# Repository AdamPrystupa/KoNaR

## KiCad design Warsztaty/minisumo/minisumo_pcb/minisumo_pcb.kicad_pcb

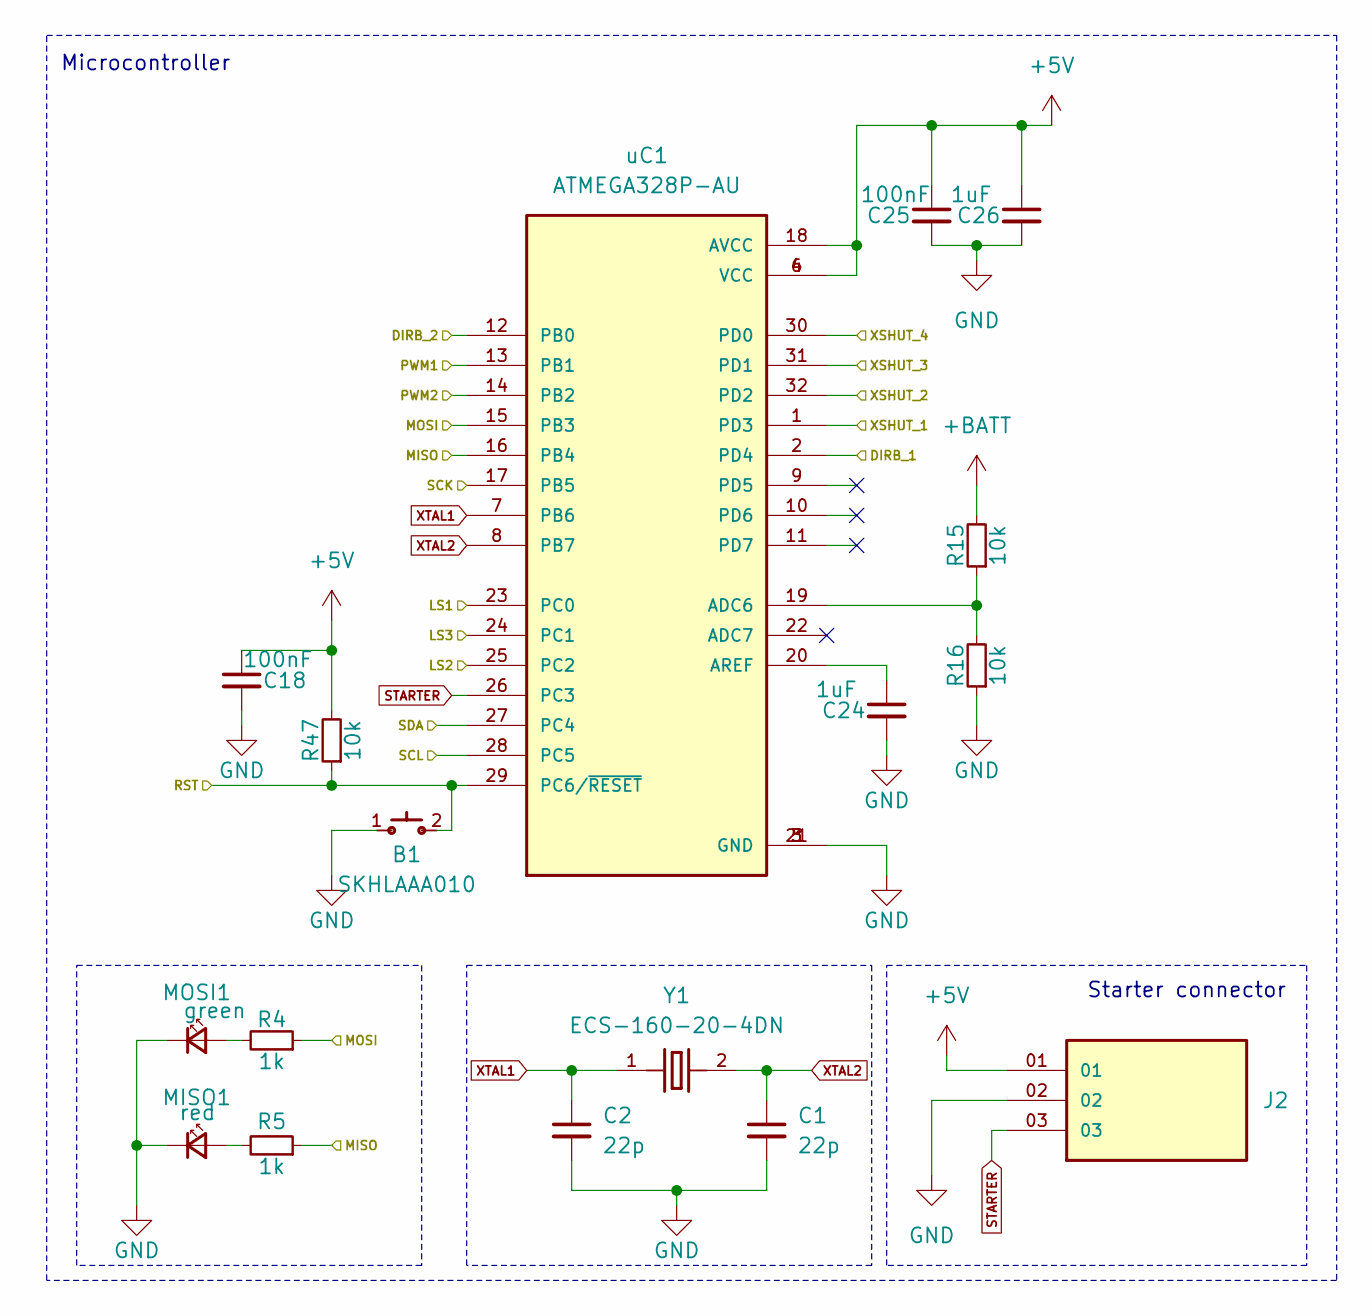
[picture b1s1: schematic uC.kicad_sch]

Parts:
B1: SKHLAAA010
C1, C2: 22p; C_0805_2012Metric
C18, C25: 100nF; C_0805_2012Metric
C24, C26: 1uF; C_0805_2012Metric
J2: MTSW-103-23-F-S-235; SAMTEC_MTSW-103-23-F-S-235; PARTREV R
MISO1: red; LED_0805_2012Metric
MOSI1: green; LED_0805_2012Metric
R4, R5: 1k; R_0805_2012Metric
R15, R16: 10k; R_0805_2012Metric
R47: 10k; R_0805_2012Metric_Pad1.20x1.40mm_HandSolder
Y1: ECS-160-20-4DN; XTAL_ECS-160-20-4DN
uC1: ATMEGA328P-AU; QFP80P900X900X120-32N; PARTREV 8271A

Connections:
+5V: C18.1, C25.1, C26.1, J2.01, R47.2, uC1.4 (VCC), uC1.6 (VCC), uC1.18 (AVCC); also elsewhere on the board
+BATT: R15.2; also elsewhere on the board
/inverter/DIRB_1: uC1.2 (PD4); also elsewhere on the board
/inverter/DIRB_2: uC1.12 (PB0); also elsewhere on the board
/line_sensors/LS1: uC1.23 (PC0); also elsewhere on the board
/line_sensors/LS2: uC1.25 (PC2); also elsewhere on the board
/line_sensors/LS3: uC1.24 (PC1); also elsewhere on the board
/motor_driver1/PWM1: uC1.13 (PB1); also elsewhere on the board
/motor_driver2/PWM2: uC1.14 (PB2); also elsewhere on the board
/programming_connector/MISO: R5.1, uC1.16 (PB4); also elsewhere on the board
/programming_connector/MOSI: R4.1, uC1.15 (PB3); also elsewhere on the board
/programming_connector/RST: B1.2, R47.1, uC1.29 (PC6/~RESET); also elsewhere on the board
/programming_connector/SCK: uC1.17 (PB5); also elsewhere on the board
/sensor1/SCL: uC1.28 (PC5); also elsewhere on the board
/sensor1/SDA: uC1.27 (PC4); also elsewhere on the board
/sensor1/XSHUT_1: uC1.1 (PD3); also elsewhere on the board
/sensor2/XSHUT_2: uC1.32 (PD2); also elsewhere on the board
/sensor3/XSHUT_3: uC1.31 (PD1); also elsewhere on the board
/sensor4/XSHUT_4: uC1.30 (PD0); also elsewhere on the board
GND: B1.1, C1.2, C2.2, C18.2, C24.2, C25.2, C26.2, J2.02, MISO1.1 (K), MOSI1.1 (K), R16.1, uC1.3 (GND), uC1.5 (GND), uC1.21 (GND); also elsewhere on the board
unnamed: MISO1.2 (A), R5.2
unnamed: MOSI1.2 (A), R4.2
unnamed: R15.1, R16.2, uC1.19 (ADC6)
unnamed: C24.1, uC1.20 (AREF)
STARTER: J2.03, uC1.26 (PC3)
XTAL1: C2.1, Y1.1, uC1.7 (PB6)
XTAL2: C1.1, Y1.2, uC1.8 (PB7)

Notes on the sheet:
Starter connector
Microcontroller

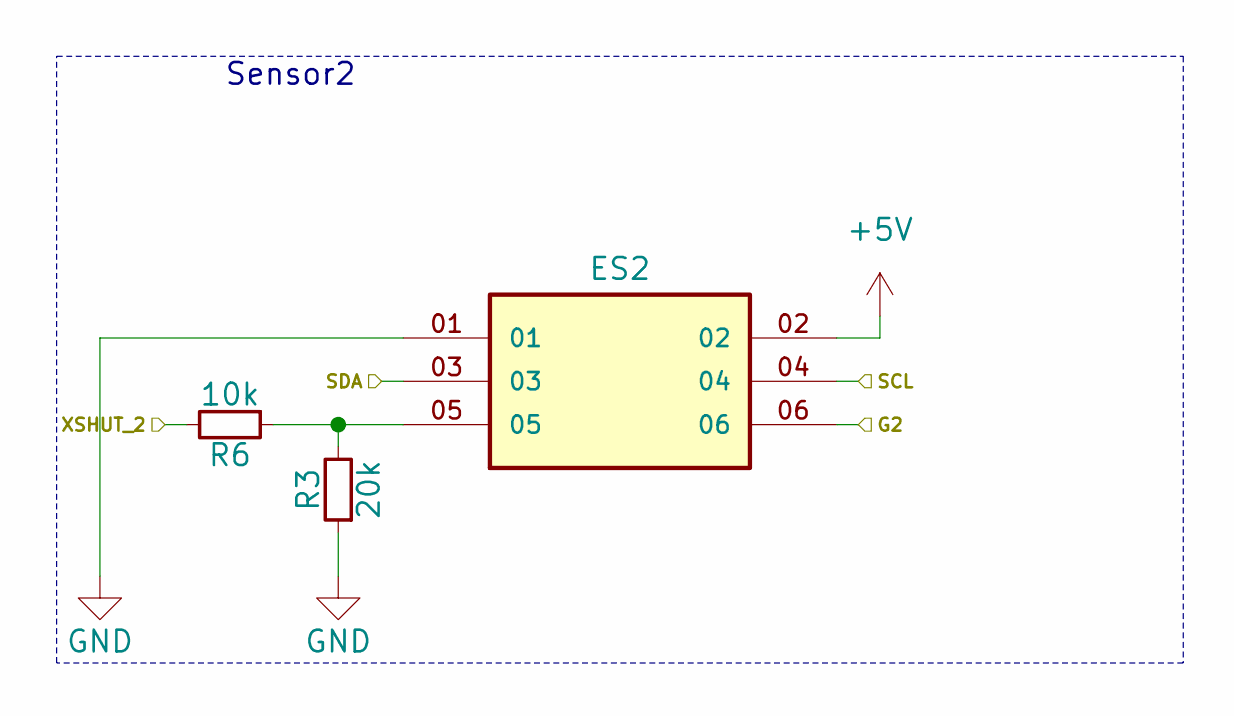
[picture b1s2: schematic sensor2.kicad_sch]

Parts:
ES2: MTSW-103-23-F-D-230; SAMTEC_MTSW-103-23-F-D-230; PARTREV R
R3: 20k; R_0805_2012Metric
R6: 10k; R_0805_2012Metric

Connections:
+5V: ES2.02; also elsewhere on the board
/sensor1/SCL: ES2.04; also elsewhere on the board
/sensor1/SDA: ES2.03; also elsewhere on the board
/sensor2/G2: ES2.06
/sensor2/XSHUT_2: R6.2; also elsewhere on the board
GND: ES2.01, R3.1; also elsewhere on the board
unnamed: ES2.05, R3.2, R6.1

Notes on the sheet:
Sensor2

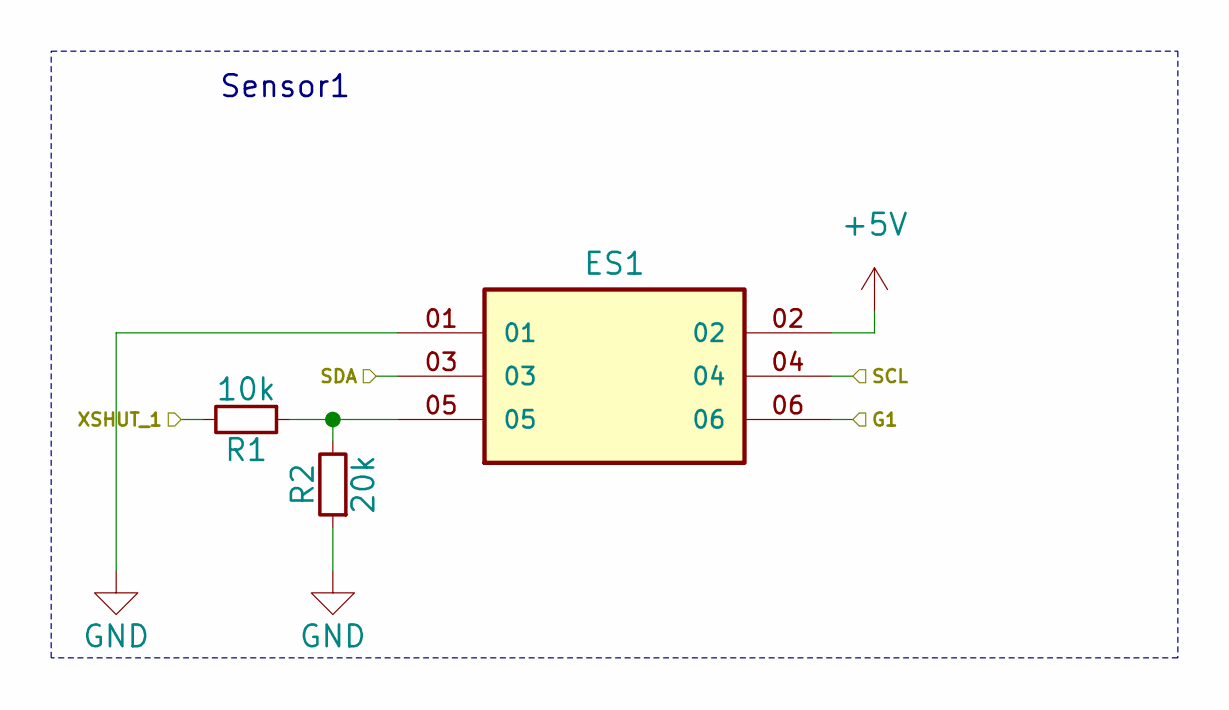
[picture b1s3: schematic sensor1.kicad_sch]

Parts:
ES1: MTSW-103-23-F-D-230; SAMTEC_MTSW-103-23-F-D-230; PARTREV R
R1: 10k; R_0805_2012Metric
R2: 20k; R_0805_2012Metric

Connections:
+5V: ES1.02; also elsewhere on the board
/sensor1/G1: ES1.06
/sensor1/SCL: ES1.04; also elsewhere on the board
/sensor1/SDA: ES1.03; also elsewhere on the board
/sensor1/XSHUT_1: R1.2; also elsewhere on the board
GND: ES1.01, R2.1; also elsewhere on the board
unnamed: ES1.05, R1.1, R2.2

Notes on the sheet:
Sensor1

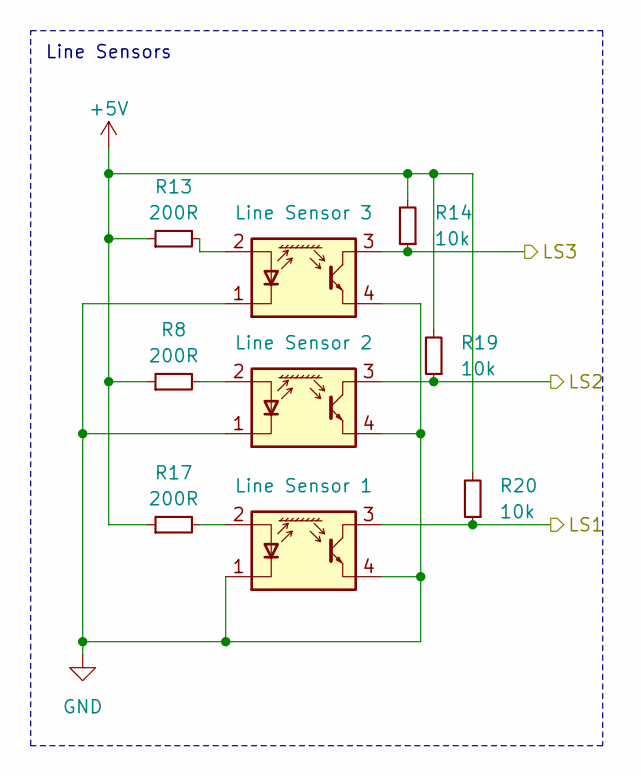
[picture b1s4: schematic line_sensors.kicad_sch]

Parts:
LS1, LS2, LS3: ITR8307-S17-TR8; Everlight_ITR1201SR10AR
R8, R13, R17: 200R; R_0805_2012Metric
R14, R19, R20: 10k; R_0805_2012Metric

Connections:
+5V: R8.1, R13.1, R14.2, R17.1, R19.2, R20.2; also elsewhere on the board
/line_sensors/LS1: LS1.3, R20.1; also elsewhere on the board
/line_sensors/LS2: LS2.3, R19.1; also elsewhere on the board
/line_sensors/LS3: LS3.3, R14.1; also elsewhere on the board
GND: LS1.1 (K), LS1.4, LS2.1 (K), LS2.4, LS3.1 (K), LS3.4; also elsewhere on the board
unnamed: LS1.2 (A), R17.2
unnamed: LS2.2 (A), R8.2
unnamed: LS3.2 (A), R13.2

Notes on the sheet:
Line Sensors

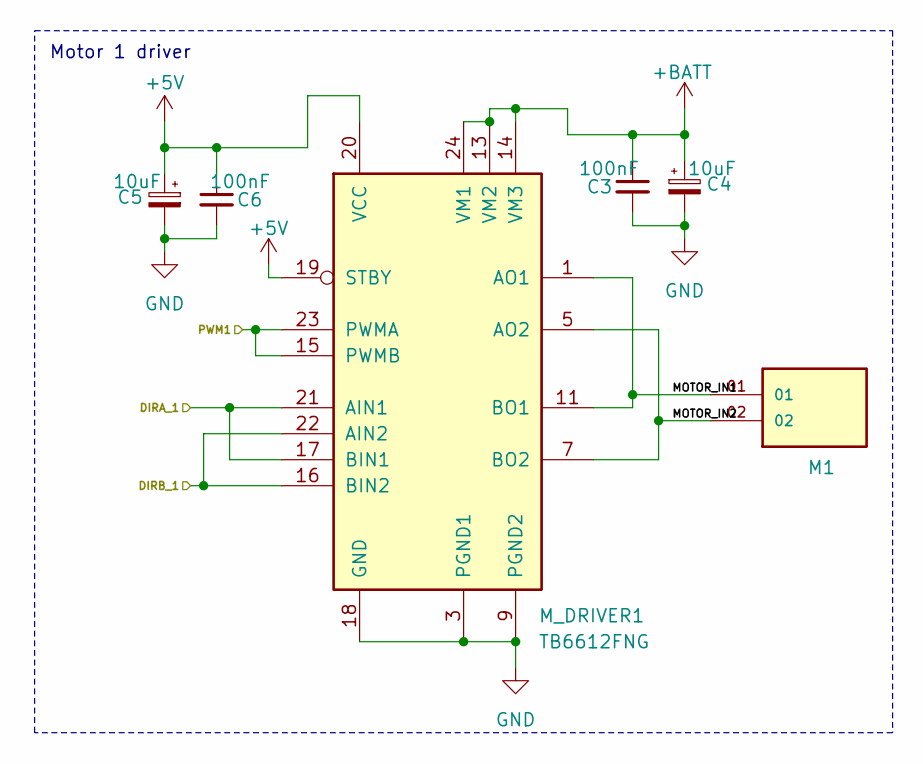
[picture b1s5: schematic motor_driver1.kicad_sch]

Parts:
C3, C6: 100nF; C_0805_2012Metric
C4, C5: 10uF; CP_EIA-3528-12_Kemet-T
M1: HTSW-102-08-L-S; SAMTEC_HTSW-102-08-L-S
M_DRIVER1: TB6612FNG; SSOP-24_5.3x8.2mm_P0.65mm

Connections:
+5V: C5.1, C6.1, M_DRIVER1.19 (STBY), M_DRIVER1.20 (VCC); also elsewhere on the board
+BATT: C3.1, C4.1, M_DRIVER1.13 (VM2), M_DRIVER1.14 (VM3), M_DRIVER1.24 (VM1); also elsewhere on the board
/inverter/DIRA_1: M_DRIVER1.17 (BIN1), M_DRIVER1.21 (AIN1); also elsewhere on the board
/inverter/DIRB_1: M_DRIVER1.16 (BIN2), M_DRIVER1.22 (AIN2); also elsewhere on the board
/motor_driver1/MOTOR_IN1: M1.01, M_DRIVER1.1 (AO1), M_DRIVER1.2 (AO1), M_DRIVER1.11 (BO1), M_DRIVER1.12 (BO1)
/motor_driver1/MOTOR_IN2: M1.02, M_DRIVER1.5 (AO2), M_DRIVER1.6 (AO2), M_DRIVER1.7 (BO2), M_DRIVER1.8 (BO2)
/motor_driver1/PWM1: M_DRIVER1.15 (PWMB), M_DRIVER1.23 (PWMA); also elsewhere on the board
GND: C3.2, C4.2, C5.2, C6.2, M_DRIVER1.3 (PGND1), M_DRIVER1.4 (PGND1), M_DRIVER1.9 (PGND2), M_DRIVER1.10 (PGND2), M_DRIVER1.18 (GND); also elsewhere on the board

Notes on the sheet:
Motor 1 driver

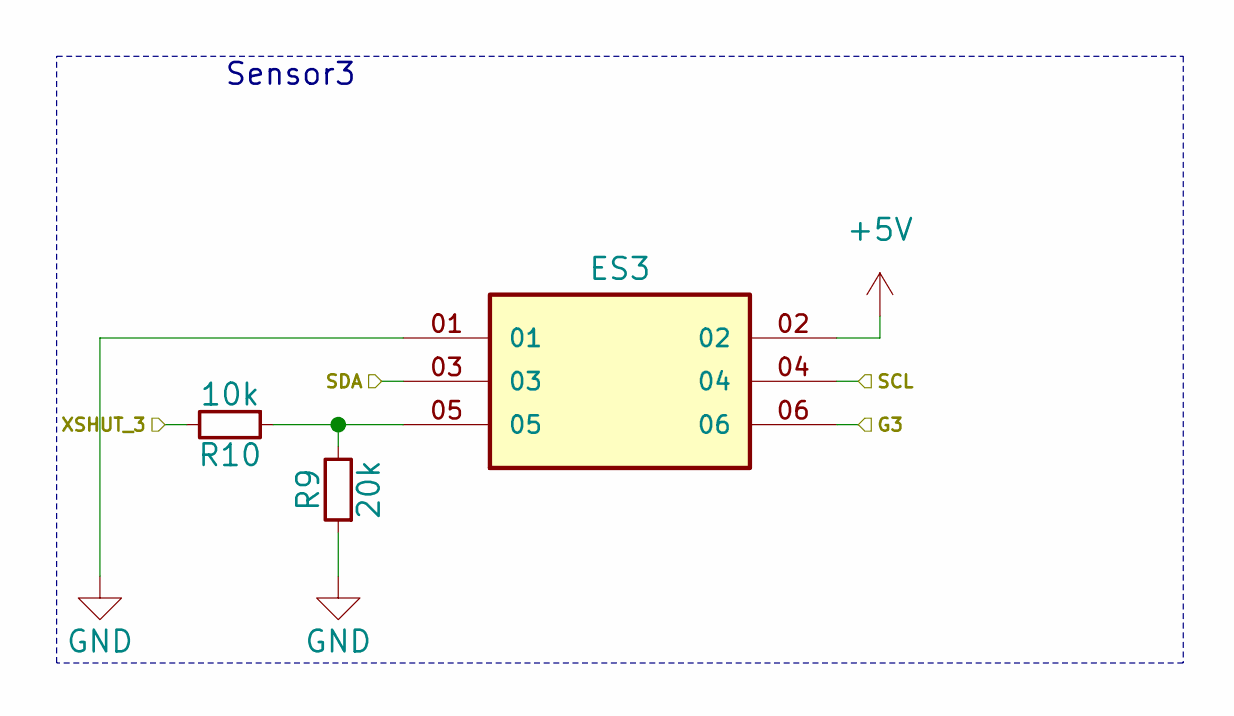
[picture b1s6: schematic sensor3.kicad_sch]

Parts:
ES3: MTSW-103-23-F-D-230; SAMTEC_MTSW-103-23-F-D-230; PARTREV R
R9: 20k; R_0805_2012Metric
R10: 10k; R_0805_2012Metric

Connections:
+5V: ES3.02; also elsewhere on the board
/sensor1/SCL: ES3.04; also elsewhere on the board
/sensor1/SDA: ES3.03; also elsewhere on the board
/sensor3/G3: ES3.06
/sensor3/XSHUT_3: R10.2; also elsewhere on the board
GND: ES3.01, R9.1; also elsewhere on the board
unnamed: ES3.05, R9.2, R10.1

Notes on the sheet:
Sensor3

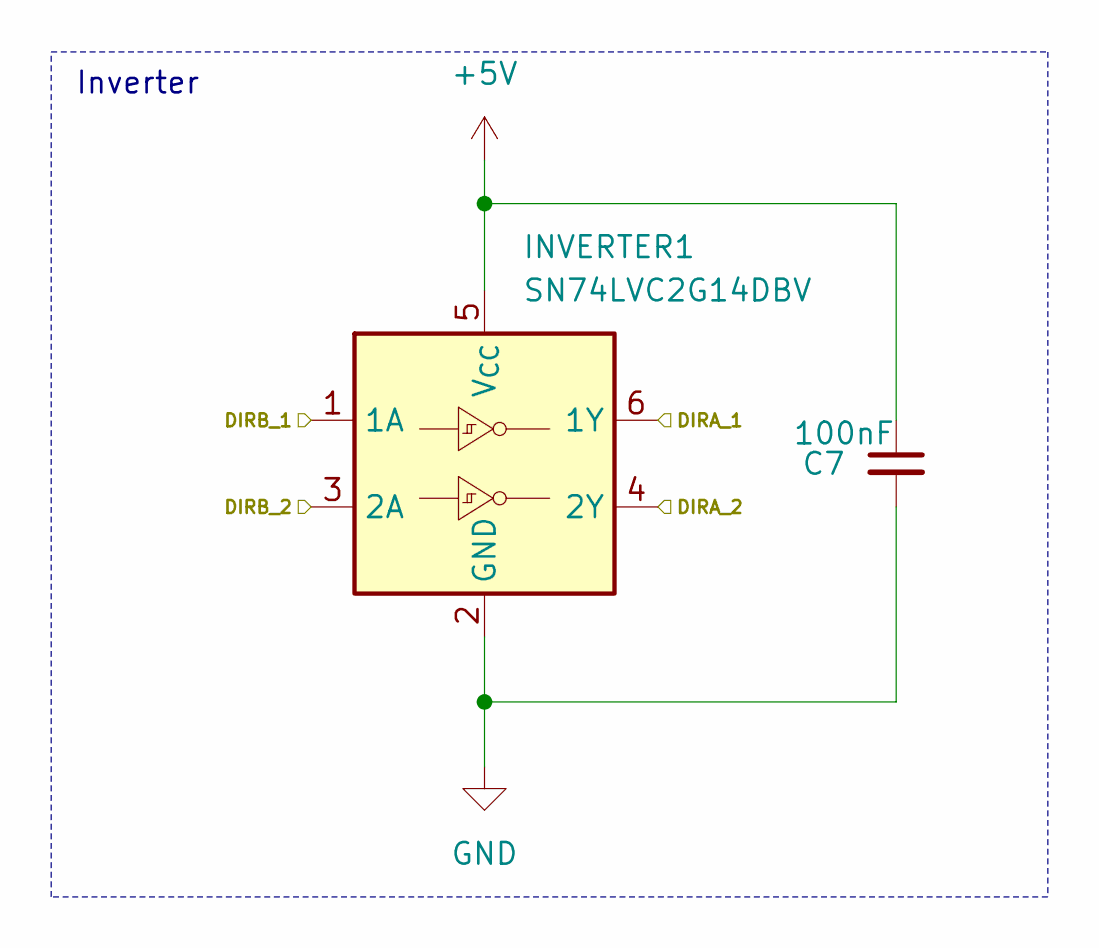
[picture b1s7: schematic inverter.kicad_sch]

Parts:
C7: 100nF; C_0805_2012Metric
INVERTER1: SN74LVC2G14DBV; SOT-23-6

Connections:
+5V: C7.1, INVERTER1.5 (V_{CC}); also elsewhere on the board
/inverter/DIRA_1: INVERTER1.6 (1Y); also elsewhere on the board
/inverter/DIRA_2: INVERTER1.4 (2Y); also elsewhere on the board
/inverter/DIRB_1: INVERTER1.1 (1A); also elsewhere on the board
/inverter/DIRB_2: INVERTER1.3 (2A); also elsewhere on the board
GND: C7.2, INVERTER1.2 (GND); also elsewhere on the board

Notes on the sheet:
Inverter

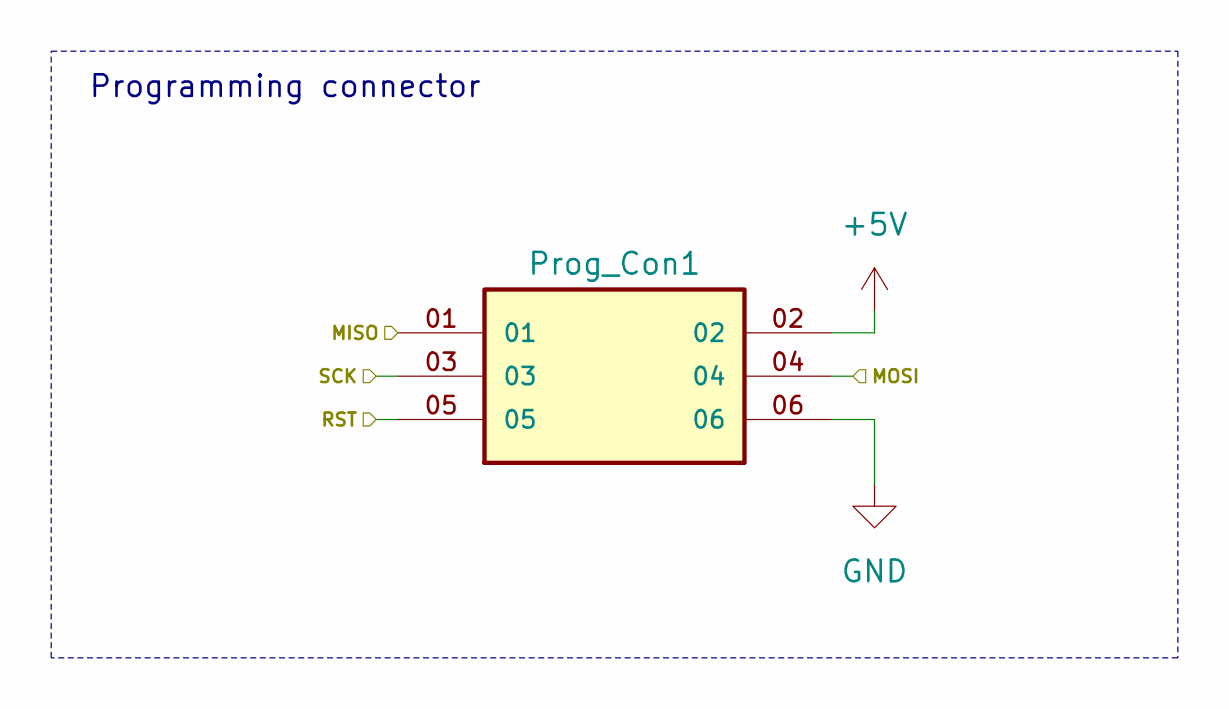
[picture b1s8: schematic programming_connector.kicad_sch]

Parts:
Prog_Con1: MTSW-103-23-F-D-230; SAMTEC_MTSW-103-23-F-D-230; PARTREV R

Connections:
+5V: Prog_Con1.02; also elsewhere on the board
/programming_connector/MISO: Prog_Con1.01; also elsewhere on the board
/programming_connector/MOSI: Prog_Con1.04; also elsewhere on the board
/programming_connector/RST: Prog_Con1.05; also elsewhere on the board
/programming_connector/SCK: Prog_Con1.03; also elsewhere on the board
GND: Prog_Con1.06; also elsewhere on the board

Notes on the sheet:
Programming connector

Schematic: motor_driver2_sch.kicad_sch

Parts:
C27, C30: 10uF; CP_EIA-3528-12_Kemet-T
C28, C29: 100nF; C_0805_2012Metric
M2: HTSW-102-08-L-S; SAMTEC_HTSW-102-08-L-S
M_DRIVER2: TB6612FNG; SSOP-24_5.3x8.2mm_P0.65mm

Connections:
+5V: C27.1, C28.1, M_DRIVER2.19 (STBY), M_DRIVER2.20 (VCC); also elsewhere on the board
+BATT: C29.1, C30.1, M_DRIVER2.13 (VM2), M_DRIVER2.14 (VM3), M_DRIVER2.24 (VM1); also elsewhere on the board
/inverter/DIRA_2: M_DRIVER2.17 (BIN1), M_DRIVER2.21 (AIN1); also elsewhere on the board
/inverter/DIRB_2: M_DRIVER2.16 (BIN2), M_DRIVER2.22 (AIN2); also elsewhere on the board
/motor_driver2/MOTOR_IN1: M2.01, M_DRIVER2.1 (AO1), M_DRIVER2.2 (AO1), M_DRIVER2.11 (BO1), M_DRIVER2.12 (BO1)
/motor_driver2/MOTOR_IN2: M2.02, M_DRIVER2.5 (AO2), M_DRIVER2.6 (AO2), M_DRIVER2.7 (BO2), M_DRIVER2.8 (BO2)
/motor_driver2/PWM2: M_DRIVER2.15 (PWMB), M_DRIVER2.23 (PWMA); also elsewhere on the board
GND: C27.2, C28.2, C29.2, C30.2, M_DRIVER2.3 (PGND1), M_DRIVER2.4 (PGND1), M_DRIVER2.9 (PGND2), M_DRIVER2.10 (PGND2), M_DRIVER2.18 (GND); also elsewhere on the board

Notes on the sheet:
Motor 2 driver

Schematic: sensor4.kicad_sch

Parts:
ES4: MTSW-103-23-F-D-230; SAMTEC_MTSW-103-23-F-D-230; PARTREV R
R11: 20k; R_0805_2012Metric
R12: 10k; R_0805_2012Metric

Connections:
+5V: ES4.02; also elsewhere on the board
/sensor1/SCL: ES4.04; also elsewhere on the board
/sensor1/SDA: ES4.03; also elsewhere on the board
/sensor4/G4: ES4.06
/sensor4/XSHUT_4: R12.2; also elsewhere on the board
GND: ES4.01, R11.1; also elsewhere on the board
unnamed: ES4.05, R11.2, R12.1

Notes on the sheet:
Sensor4

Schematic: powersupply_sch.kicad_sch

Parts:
+5V1: green; LED_0805_2012Metric
BATT1: HTSW-102-08-L-S; SAMTEC_HTSW-102-08-L-S
C9, C10: 10u; CP_EIA-3528-12_Kemet-T
Q1: PMOS; SOT-23-3
R7: 180; R_0805_2012Metric
S1: 1101M2S3CQE2; SW_1101M2S3CQE2
U7: LM1117S-5.0; SOT-223

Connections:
+5V: C10.1, R7.1, U7.2 (VO); also elsewhere on the board
+BATT: C9.1, Q1.3 (S), U7.3 (VI); also elsewhere on the board
+IN: BATT1.02, S1.2
+OUT: Q1.1 (D), S1.1
GND: +5V1.1 (K), BATT1.01, C9.2, C10.2, Q1.2 (G), U7.1 (GND); also elsewhere on the board
unnamed: +5V1.2 (A), R7.2

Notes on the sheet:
Voltage regulator 5V
POWER

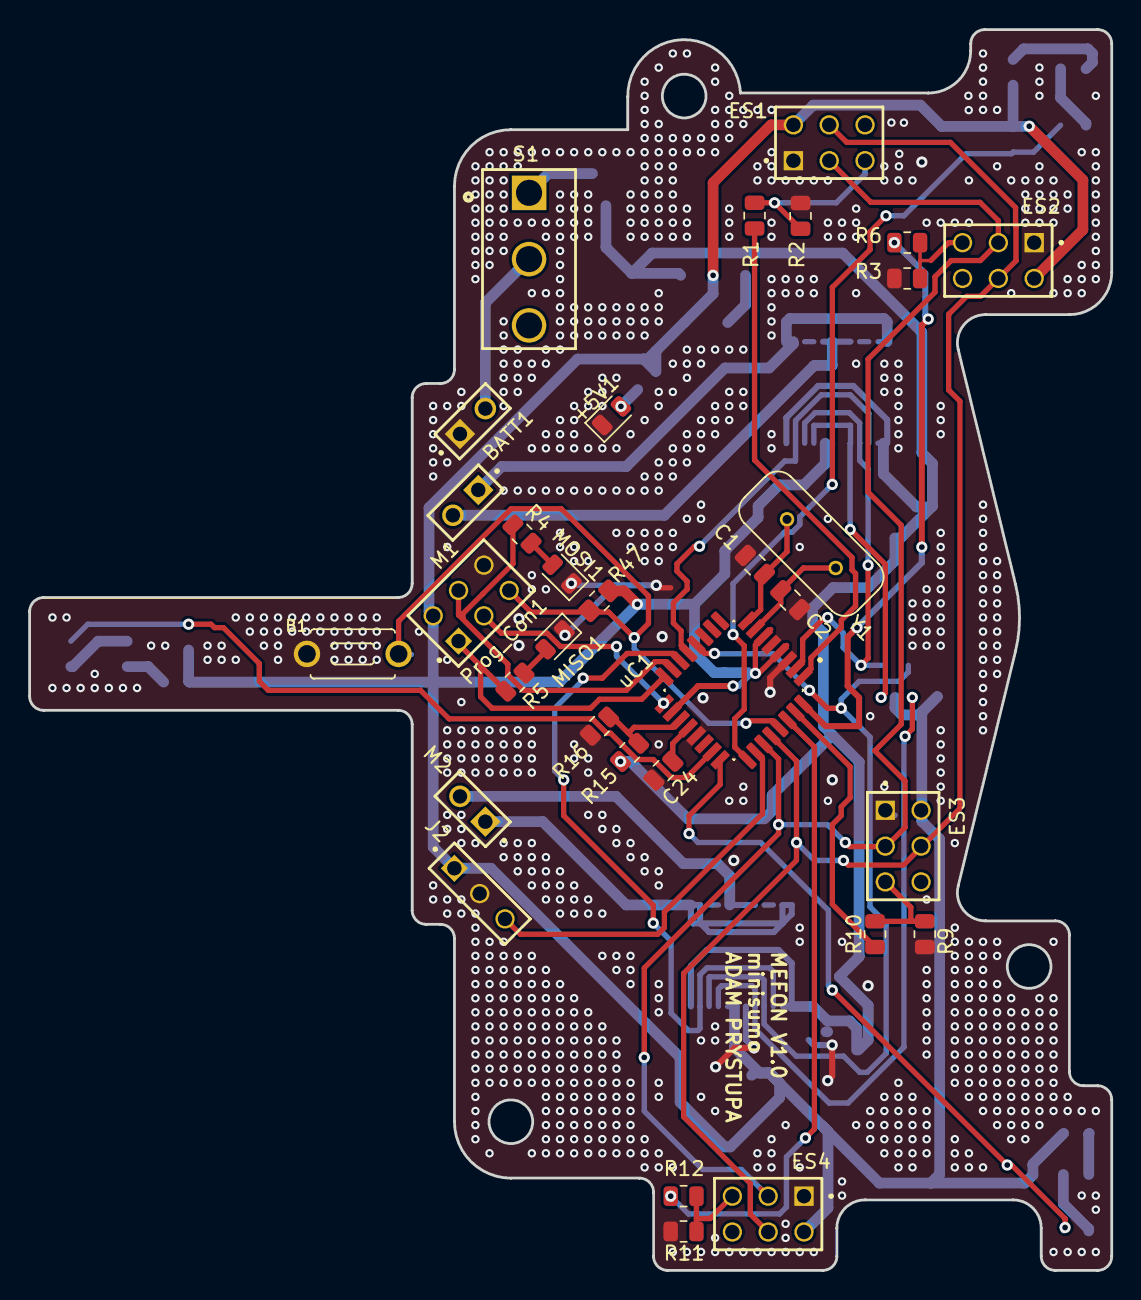
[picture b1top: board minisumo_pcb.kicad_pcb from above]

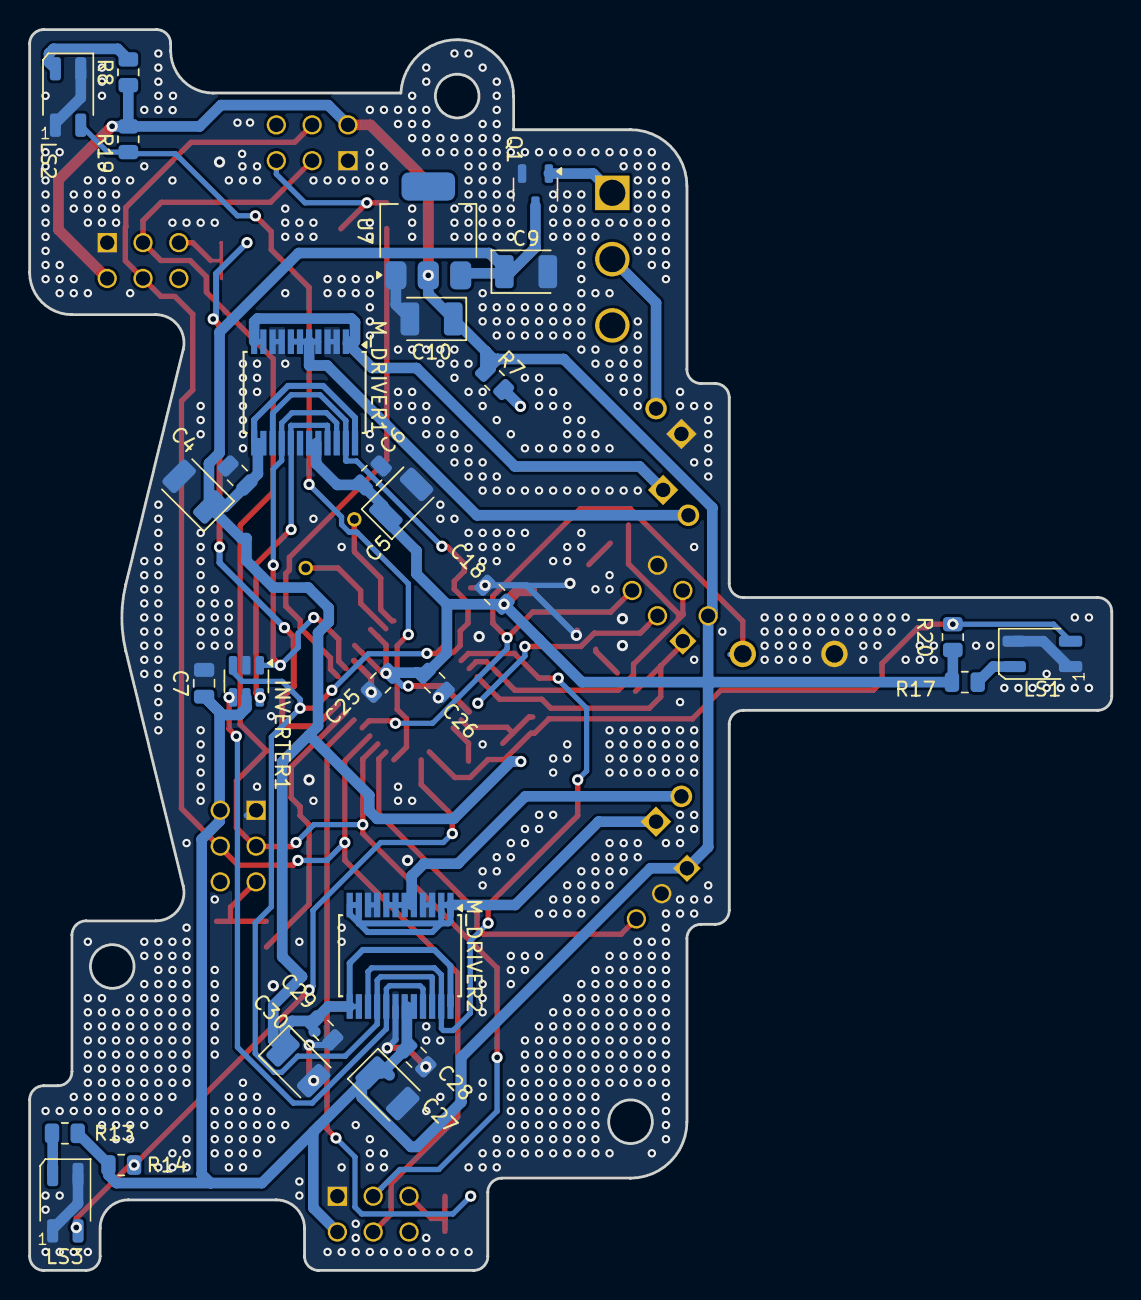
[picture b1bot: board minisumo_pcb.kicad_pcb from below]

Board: 2 copper layers, 76.8 x 88.0 mm, 61 parts (29 on the bottom side), 43 nets.

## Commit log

2024-05-03 uzupełnienie repo
2024-05-03 naprawa segregator
2024-05-04 laczenie hierarchiczne schematu
2024-05-04 wstepnie skonczony schemat
2024-05-05 wstepnie gotowy schemat
2024-05-05 chyba gotowy schemat
2024-05-12 stan przed usunięciem jednego czujnika lini
2024-05-25 Wstępny wyglad robota i płytki
2024-05-27 koncowy projekt plytki i chyba model tez
2024-05-30 prawdopodobnie koncowa wersja płytki
2024-05-30 ostateczna wersja mechaniczna
2024-05-30 ostateczna wersja plytki
2024-05-30 dodane modele 3d elektroniki
2024-05-31 wersja ostateczna plytki - gotowe gerbery do zamowienia
2024-05-31 wersja ostateczna plytki - gotowe gerbery do zamowienia
2024-06-03 ostatnie poprawki
2024-06-04 ostateczna wersja płytki
